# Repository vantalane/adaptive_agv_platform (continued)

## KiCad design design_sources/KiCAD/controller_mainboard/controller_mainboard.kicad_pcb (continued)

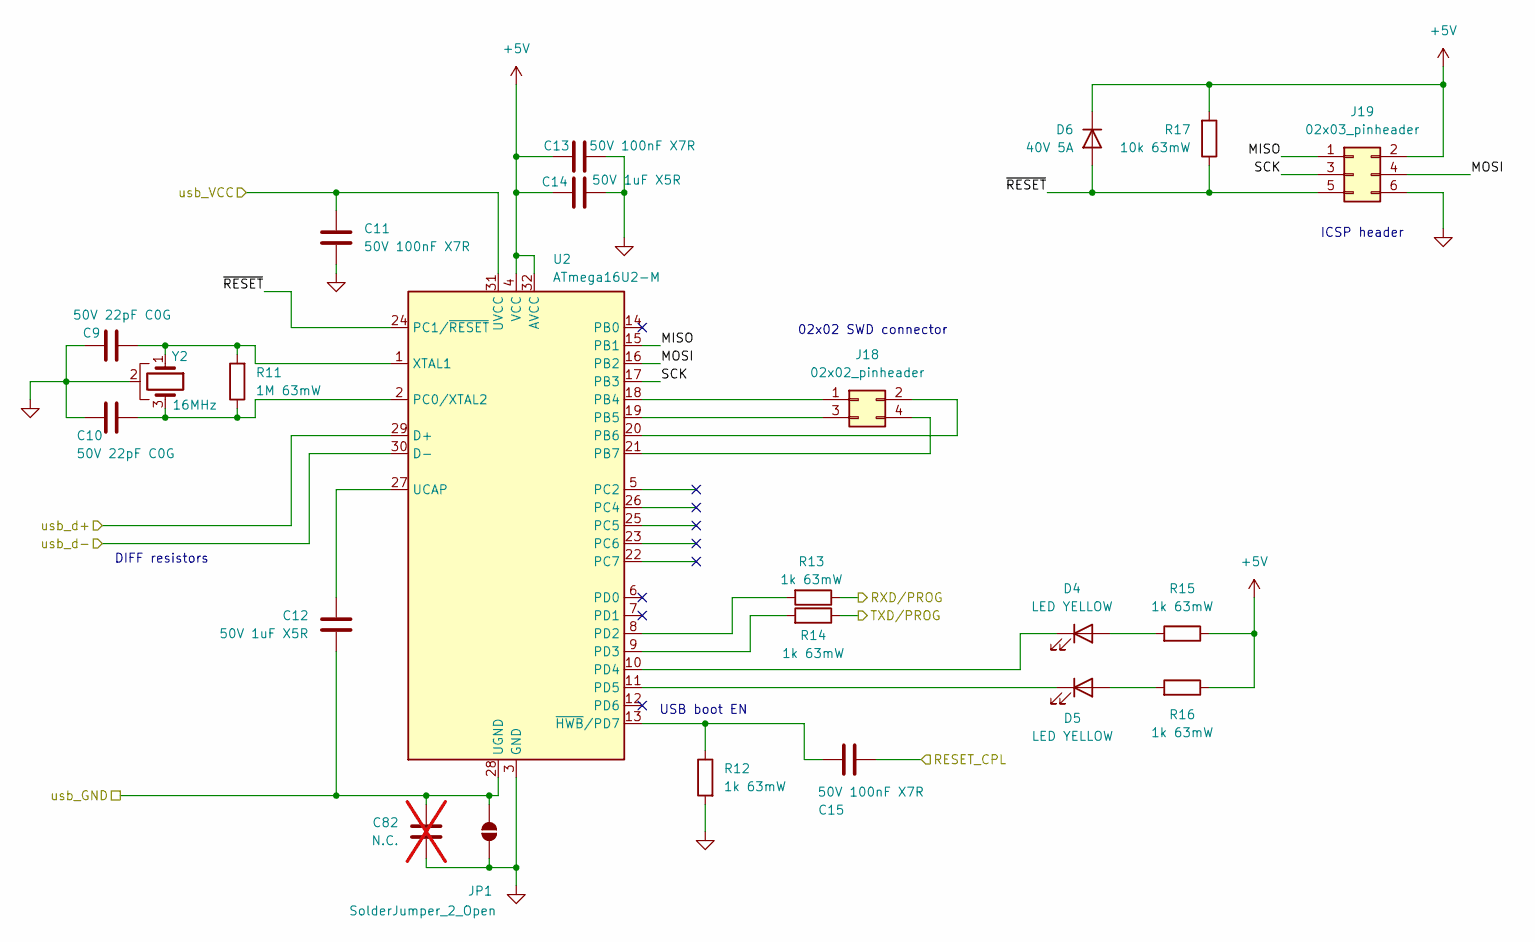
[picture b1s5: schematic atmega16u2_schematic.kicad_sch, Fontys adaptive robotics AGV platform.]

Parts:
C9, C10: 50V 22pF C0G; C_0402_1005Metric; JLCPCB C1555
C11, C13, C15: 50V 100nF X7R; C_0603_1608Metric; JLCPCB C14663
C12, C14: 50V 1uF X5R; C_0603_1608Metric; JLCPCB C15849
C82: N.C.; C_0603_1608Metric; not fitted
D4, D5: LED YELLOW; LED_0603_1608Metric; JLCPCB C72038
D6: 40V 5A; D_SMA; JLCPCB C22452
J18: 02x02_pinheader; PinHeader_2x02_P2.54mm_Vertical
J19: 02x03_pinheader; PinHeader_2x03_P2.54mm_Vertical
JP1: SolderJumper_2_Open; SolderJumper-2_P1.3mm_Open_RoundedPad1.0x1.5mm
R11: 1M 63mW; R_0603_1608Metric
R12, R13, R14, R15, R16: 1k 63mW; R_0402_1005Metric; JLCPCB C11702
R17: 10k 63mW; R_0402_1005Metric; JLCPCB C25744
U2: ATmega16U2-M; QFN-32-1EP_5x5mm_P0.5mm_EP3.1x3.1mm
Y2: 16MHz; Resonator_SMD_Murata_CSTxExxV-3Pin_3.0x1.1mm; JLCPCB C783275

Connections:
+5V: C13.1, C14.1, D6.1 (K), J19.2, R15.1, R16.1, R17.2, U2.4 (VCC), U2.32 (AVCC); also elsewhere on the board
/ATmega16u2/MISO: J19.1, U2.15 (PB1)
/ATmega16u2/MOSI: J19.4, U2.16 (PB2)
/ATmega16u2/SCK: J19.3, U2.17 (PB3)
/ATmega16u2/~RESET: D6.2 (A), J19.5, R17.1, U2.24 (PC1/~RESET)
/D0: R14.1; also elsewhere on the board
/D1: R13.1; also elsewhere on the board
/USB_D_N: U2.30 (D-); also elsewhere on the board
/USB_D_P: U2.29 (D+); also elsewhere on the board
/USB_GND: C12.2, C82.2, JP1.2 (B), U2.28 (UGND); also elsewhere on the board
/USB_VBUS: C11.1, U2.31 (UVCC); also elsewhere on the board
/~mega2560_reset: C15.2; also elsewhere on the board
GND: C9.1, C10.1, C11.2, C13.2, C14.2, C82.1, J19.6, JP1.1 (A), R12.2, U2.3 (GND), U2.33 (GND), Y2.2; also elsewhere on the board
unnamed: D4.2 (A), R15.2
unnamed: D4.1 (K), U2.10 (PD4)
unnamed: D5.2 (A), R16.2
unnamed: D5.1 (K), U2.11 (PD5)
unnamed: J18.1, U2.18 (PB4)
unnamed: J18.2, U2.20 (PB6)
unnamed: J18.3, U2.19 (PB5)
unnamed: J18.4, U2.21 (PB7)
unnamed: C10.2, R11.1, U2.2 (PC0/XTAL2), Y2.3
unnamed: R13.2, U2.8 (PD2)
unnamed: R14.2, U2.9 (PD3)
unnamed: C12.1, U2.27 (UCAP)
unnamed: C9.2, R11.2, U2.1 (XTAL1), Y2.1
unnamed: C15.1, R12.1, U2.13 (~HWB/PD7)

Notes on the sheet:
02x02 SWD connector
USB boot EN
DIFF resistors
ICSP header

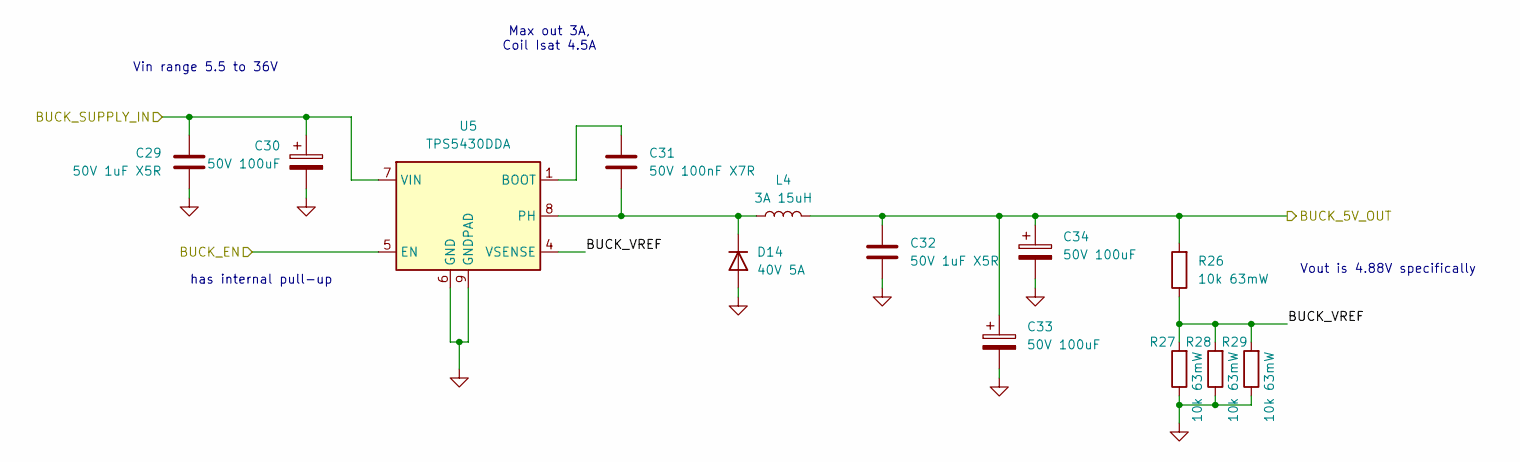
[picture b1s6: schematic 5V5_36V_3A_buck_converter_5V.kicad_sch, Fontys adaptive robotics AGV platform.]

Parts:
C29, C32: 50V 1uF X5R; C_0603_1608Metric; JLCPCB C15849
C30, C33, C34: 50V 100uF; CP_Elec_8x10.5; JLCPCB C5246561
C31: 50V 100nF X7R; C_0603_1608Metric; JLCPCB C14663
D14: 40V 5A; D_SMA; JLCPCB C22452
L4: 3A 15uH; L_APV_APH0630; JLCPCB C177243
R26, R27, R28, R29: 10k 63mW; R_0402_1005Metric; JLCPCB C25744
U5: TPS5430DDA; TI_SO-PowerPAD-8_ThermalVias; JLCPCB C9864

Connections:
+5V: C32.1, C33.1, C34.1, L4.2, R26.2; also elsewhere on the board
+BATT: C29.1, C30.1, U5.7 (VIN); also elsewhere on the board
/5V_3A_buck_converter/BUCK_EN: U5.5 (EN); also elsewhere on the board
/5V_3A_buck_converter/BUCK_VREF: R26.1, R27.2, R28.2, R29.2, U5.4 (VSENSE)
GND: C29.2, C30.2, C32.2, C33.2, C34.2, D14.2 (A), R27.1, R28.1, R29.1, U5.6 (GND), U5.9 (GNDPAD); also elsewhere on the board
unnamed: C31.2, D14.1 (K), L4.1, U5.8 (PH)
unnamed: C31.1, U5.1 (BOOT)

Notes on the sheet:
Vout is 4.88V specifically
has internal pull-up
Max out 3A, Coil Isat 4.5A
Vin range 5.5 to 36V

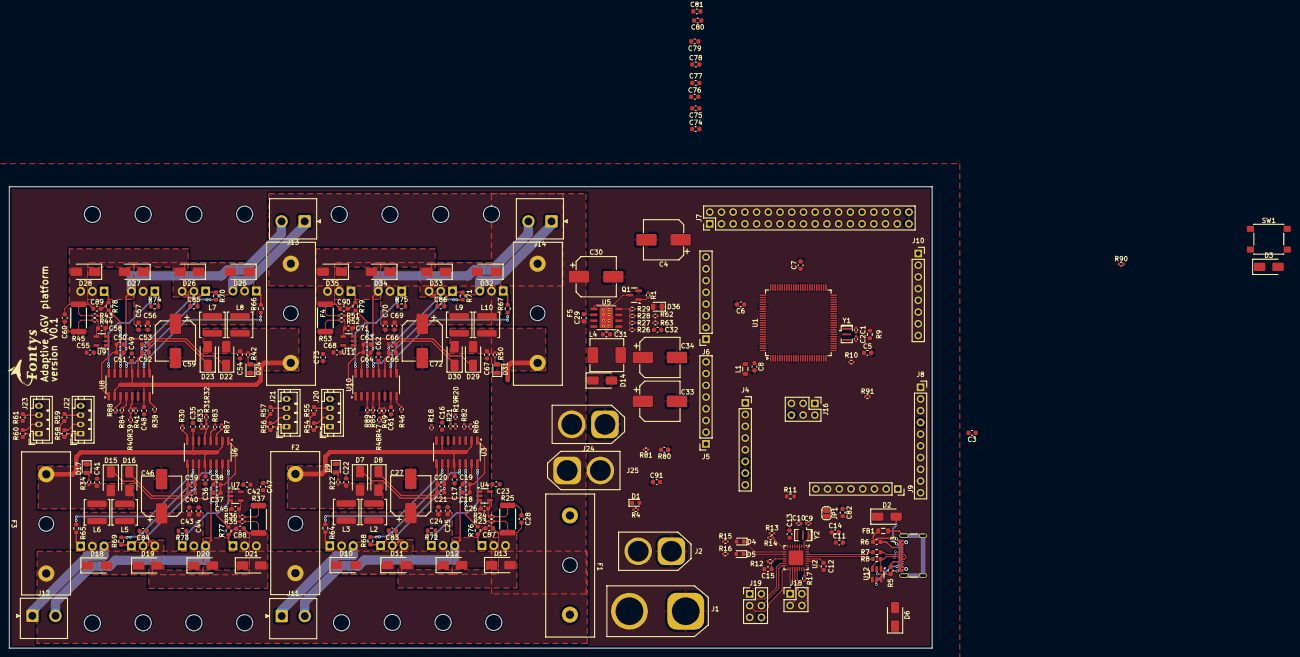
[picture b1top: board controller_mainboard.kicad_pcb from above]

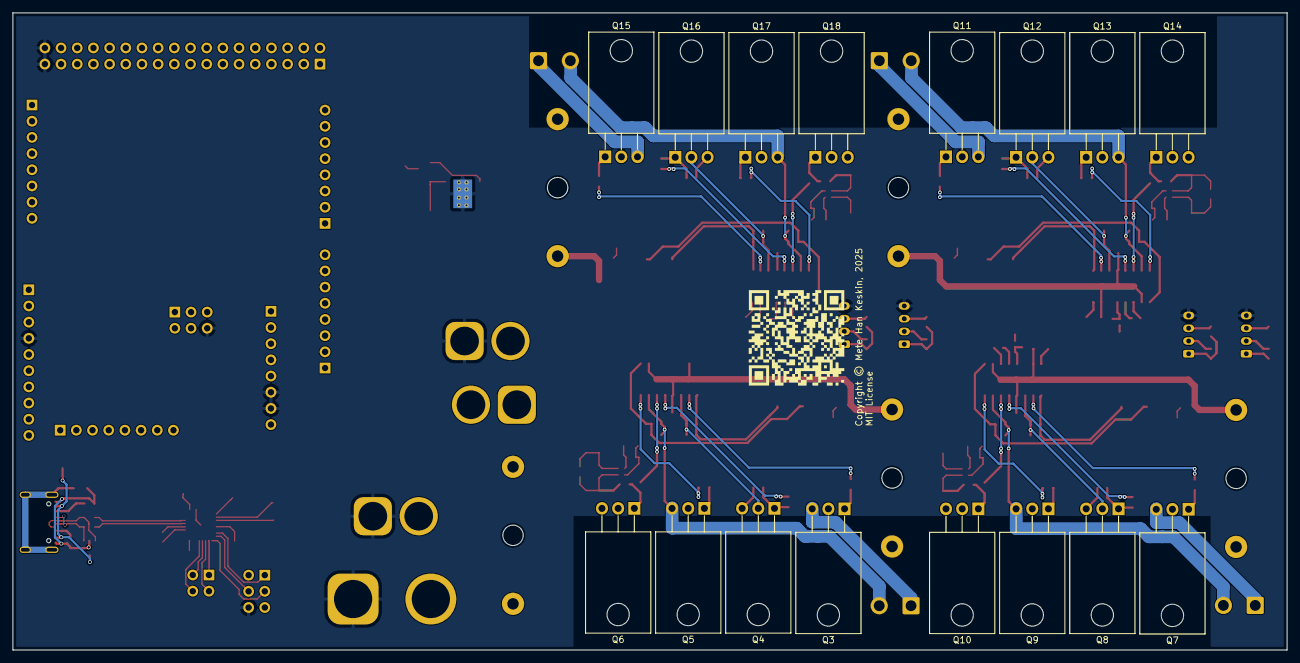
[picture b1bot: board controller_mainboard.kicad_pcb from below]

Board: 4 copper layers, 200.0 x 100.0 mm, 288 parts (16 on the bottom side), 211 nets.

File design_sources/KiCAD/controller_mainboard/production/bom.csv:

Designator,Footprint,Quantity,Value,LCSC Part #
"C1, C10, C2, C9, C92, C93",0402,6,50V 22pF C0G,
"C11, C13, C15, C17, C23, C26, C28, C3, C31, C36, C42, C45, C47, C49, C5, C55, C58, C6, C60, C62, C68, C71, C73, C8, C91",0603,25,50V 100nF X7R,
"C12, C14, C16, C18, C19, C20, C21, C22, C24, C25, C29, C32, C35, C37, C38, C39, C40, C41, C43, C44, C48, C50, C51, C52, C53, C54, C56, C57, C61, C63, C64, C65, C66, C67, C69, C7, C70",0603,37,50V 1uF X5R,
"C27, C30, C33, C34, C4, C46, C59, C72",CP_Elec_8x10.5,8,50V 100uF,
"C74, C75, C76, C77, C78, C79, C80, C81, C82, C83, C84, C85, C86, C87, C88, C89, C90",0603,17,N.C.,
D1,0603,1,LED RED,
"D10, D11, D12, D13, D14, D15, D16, D18, D19, D2, D20, D21, D22, D23, D25, D26, D27, D28, D29, D3, D30, D32, D33, D34, D35, D6, D7, D8",D_SMA,28,40V 5A,
"D17, D24, D31, D36, D9",0805,5,LED GREEN,
"D4, D5",0603,2,LED YELLOW,
F1,BLX-A fuse holder,1,Fuse 20A,
"F2, F3, F4, F5",BLX-A fuse holder,4,5A,
FB1,0805,1,GZ2012D101TF,
J1,XT-90_Connector,1,XT-90,
"J10, J4, J5, J6, J9",PinSocket_1x08_P2.54mm_Vertical,5,01x08_2.54mm _socket,
"J11, J12, J13, J14",JST_NV_B02P-NV_1x02_P5.00mm_Vertical,4,2P_screw_term,
"J16, J19",PinHeader_2x03_P2.54mm_Vertical,2,02x03_pinheader,
J18,PinHeader_2x02_P2.54mm_Vertical,1,02x02_pinheader,
"J2, J24, J25",AMASS_XT60-M_1x02_P7.20mm_Vertical,3,XT-60,
"J20, J21, J22, J23",JST_PH_B4B-PH-K_1x04_P2.00mm_Vertical,4,01x04_JST_PH,
J3,USB_C_Receptacle_GCT_USB4105-xx-A_16P_TopMnt_Horizontal,1,USB_C_Receptacle_USB2.0_16P,
J7,PinSocket_2x18_P2.54mm_Vertical,1,02x18_2.54mm_socket,
J8,PinSocket_1x10_P2.54mm_Vertical,1,Conn_01x10_2.54mm_socket,
L1,0805,1,15mA 10uH 1.15Ohm,
"L10, L2, L3, L5, L6, L7, L8, L9",L_APV_ANR5040,8,5A 1uH,
L4,L_APV_APH0630,1,3A 15uH,
Q1,SOT-23,1,2N7002,
"Q10, Q11, Q12, Q13, Q14, Q15, Q16, Q17, Q18, Q3, Q4, Q5, Q6, Q7, Q8, Q9",TO-220-3_Horizontal_TabDown,16,IRF3205,
"R1, R10, R17, R18, R19, R20, R26, R27, R28, R29, R30, R31, R32, R38, R39, R40, R46, R47, R48, R81, R82, R83, R84, R85, R86, R87, R88, R89, R90, R91",0402,30,10k 63mW,
"R11, R9",0603,2,1M 63mW,
"R12, R13, R14, R15, R16, R22, R23, R24, R34, R35, R36, R4, R42, R43, R44, R50, R51, R52, R62, R63",0402,20,1k 63mW,
"R21, R33, R41, R49",0402,4,N.C.,
"R25, R37, R45, R53",2512,4,50m 750mW 1%,
"R5, R54, R55, R56, R57, R58, R59, R6, R60, R61, R80",0603,11,5.1K 100mW,
"R64, R65, R66, R67, R68, R69, R70, R71, R72, R73, R74, R75, R76, R77, R78, R79",0603,16,0R 100mW,
"R7, R8",0603,2,22R 100mW,
SW1,SW_SPST_PTS645,1,SW_Push,
U1,TQFP-100_14x14mm_P0.5mm,1,ATmega2560-16A,
"U10, U3, U6, U8",SOIC-16_3.9x9.9mm_P1.27mm,4,HIP4082IBZT,
"U11, U4, U7, U9",SOT-23-5,4,INA180A1IDBVR,
U12,SOT-23-6,1,USBLC6-4SC6,
U2,QFN-32-1EP_5x5mm_P0.5mm_EP3.1x3.1mm,1,ATmega16U2-M,
U5,TI_SO-PowerPAD-8_ThermalVias,1,TPS5430DDA,
"Y1, Y2",Resonator_SMD_Murata_CSTxExxV-3Pin_3.0x1.1mm,2,16MHz,

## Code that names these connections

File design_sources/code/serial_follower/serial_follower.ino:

/* WARNING, CODE IS INCOMPLETE, IT IS UP TO YOU TO COMPLETE IT */

/* ========================
      Pin Definitions 
 ======================== */

/* --- Encoder Inputs --- */
#define ENC_B4 22
#define ENC_A4 23
#define ENC_B3 24
#define ENC_A3 25
#define ENC_B2 26
#define ENC_A2 27
#define ENC_B1 28
#define ENC_A1 29

/* --- Motor Driver PWM Outputs --- */
#define MOT_DRV_PWM_B4 2
#define MOT_DRV_PWM_A4 3
#define MOT_DRV_PWM_B2 4
#define MOT_DRV_PWM_A2 5
#define MOT_DRV_PWM_A3 6
#define MOT_DRV_PWM_B3 7
#define MOT_DRV_PWM_A1 8
#define MOT_DRV_PWM_B1 9

/* --- Analog Inputs --- */
#define VBAT_ADC A3
#define MOT_CURR_V_1 A4
#define MOT_CURR_V_2 A5
#define MOT_CURR_V_3 A6
#define MOT_CURR_V_4 A7

/*
  === STUDENT TEMPLATE START ===

  This Arduino code handles serial communication with a master device.

  Serial Command Structure:
    [CMD][ARG1][ARG2]...

  Implemented Commands:
    0x01: Echo back 1 byte
    0x02: Set a GPIO pin HIGH/LOW
    0x03: Read a GPIO pin's state
    0x04: Read ADC value from analog pin
    0x05: Set PWM output on any PWM-capable pin

  Extend this sketch to:
    - Add encoder reading support
    - Add additional motor control logic
    - Implement safety or timing mechanisms

  NOTE: Ensure pin numbers are valid on your board. Use digital pins 0-53 and analog pins A0-A15.
        Use the PCBA schematic as reference. 

  === STUDENT TEMPLATE END ===
*/

void setup() {
  Serial.begin(115200);
}

/*  =====================================
                  Main Loop
    ===================================== */

void loop() {
  if (Serial.available()) {
    uint8_t command = Serial.read();

    /* */
    switch (command) {
      case 0x01: handleEcho(); break;
      case 0x02: handleSetGPIO(); break;
      case 0x03: handleReadGPIO(); break;
      case 0x04: handleReadADC(); break;
      case 0x05: handleSetPWM(); break;
      default: handleUnknownCommand(); break;
    }
  }
}



// =====================================
// Command Handlers
// =====================================
void handleEcho() {
  waitForBytes(1);
  uint8_t value = Serial.read();
  Serial.write(0x81);
  Serial.write(value);
}

void handleSetGPIO() {
  waitForBytes(2);
  uint8_t pin = Serial.read();
  uint8_t val = Serial.read();
  pinMode(pin, OUTPUT);
  digitalWrite(pin, val ? HIGH : LOW);
  Serial.write(0x82);
  Serial.write(pin);
  Serial.write(val);
}

void handleReadGPIO() {
  waitForBytes(1);
  uint8_t pin = Serial.read();
  pinMode(pin, INPUT);
  uint8_t val = digitalRead(pin);
  Serial.write(0x83);
  Serial.write(pin);
  Serial.write(val);
}

void handleReadADC() {
  waitForBytes(1);
  uint8_t analogPin = Serial.read();
  int adcVal = analogRead(analogPin);
  Serial.write(0x84);
  Serial.write(analogPin);
  Serial.write(highByte(adcVal));
  Serial.write(lowByte(adcVal));
}

void handleSetPWM() {
  waitForBytes(2);
  uint8_t pin = Serial.read();
  uint8_t pwmVal = Serial.read();
  pinMode(pin, OUTPUT);
  analogWrite(pin, pwmVal);
  Serial.write(0x85);
  Serial.write(pin);
  Serial.write(pwmVal);
}

void handleUnknownCommand() {
  Serial.write(0xFF);  // Error or unsupported command
}

// =====================================
// Utility
// =====================================
void waitForBytes(uint8_t n) {
  while (Serial.available() < n) {
    // Busy-wait (could be replaced with timeout for robustness)
  }
}

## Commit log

2025-03-01 WIP First commit, added atmega2560,atmega16u2, motor driver and root schematic sheet
2025-03-01 Commit after closing kicad
2025-03-02 Populated the schematic more, added buck.
2025-03-02 added gitignore
2025-03-02 removed backup files as project is tracked with git
2025-03-02 Continued development on the schematic. Pins wired. TODO validate.
2025-03-03 Added ESD protection ic, added footprints to all IC and loaded into pcbnew to size up the pcb size.
2025-03-03 Read through schematic to bugfix.
2025-03-03 Adjusted gitignore to ignore backups, removed backup files
2025-03-03 started initial pcb layout
2025-03-03 Slight schematic adjustments and continue on draft pcb layout
2025-03-04 Fixed gitignore
2025-03-04 Removed backups again, improved the PCB layout
2025-03-09 Made layout of motor driver ch1, will replicate layout on other channels next.
2025-03-09 Major PCB layout progress, motor drivers are routed and placed. PCB dimensions set, started ATMEGA2560 layout. Slight schematic fixes.
2025-03-09 Advanced the hardware layout further.
2025-04-03 Nearly finalized hardware layout. TODO add extra GND stitching vias, label IO numbers on silk, add cool silk drawings
2025-04-05 Worked out most DRC errs
2025-04-05 Added via&silk naming job done, added PCBA renders
2025-04-05 added extra diagram documentation backup file.
2025-04-06 Fixed more DRC errors
2025-04-06 Generated inital production files for quotation.
2025-05-07 Added documentation folder
2025-05-07 Added some spec info in documentation folder
2025-05-07 Added a spreadsheet of parts to source outside of LCSC
2025-06-15 Re-checked DRC, differing footprint warnings are fine, added production files for JLC placement and prod. TODO, maybe cool silk art at the bottom and definitive order list.
2025-06-17 writing a readme file with instructions on ordering, also wrote down discrepancies on bom vs part etc.
2025-06-17 Backup commit, will change the bom and pos file errors
2025-06-17 Changed JLCPCB field to LCSC
2025-06-17 re-generated production files after fixing lcsc field on PCB design
2025-06-17 Updated 50m750mW resistor lcsc mpn number, re-generated production files
2025-06-18 Finished README
2025-06-18 added some cool pictures
2025-06-19 Changed kicad source folder name to contain board version number, also changed 3D model of the female XT-60's to match.
2025-06-19 Expanded the readme to include prod file instructions
2025-06-19 Added LICENSE
2025-06-20 changed gitignore path to be version agnostic
2025-06-20 Added 11th step in producting ordering recipe for tinytronics assy
2025-06-25 Added code folder with serial follower template
2025-06-25 Expanded board spec file
2025-06-25 Renamed the spec file to the board design version
